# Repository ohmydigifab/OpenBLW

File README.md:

# OpenBLW
Open Biwa Lake Walker

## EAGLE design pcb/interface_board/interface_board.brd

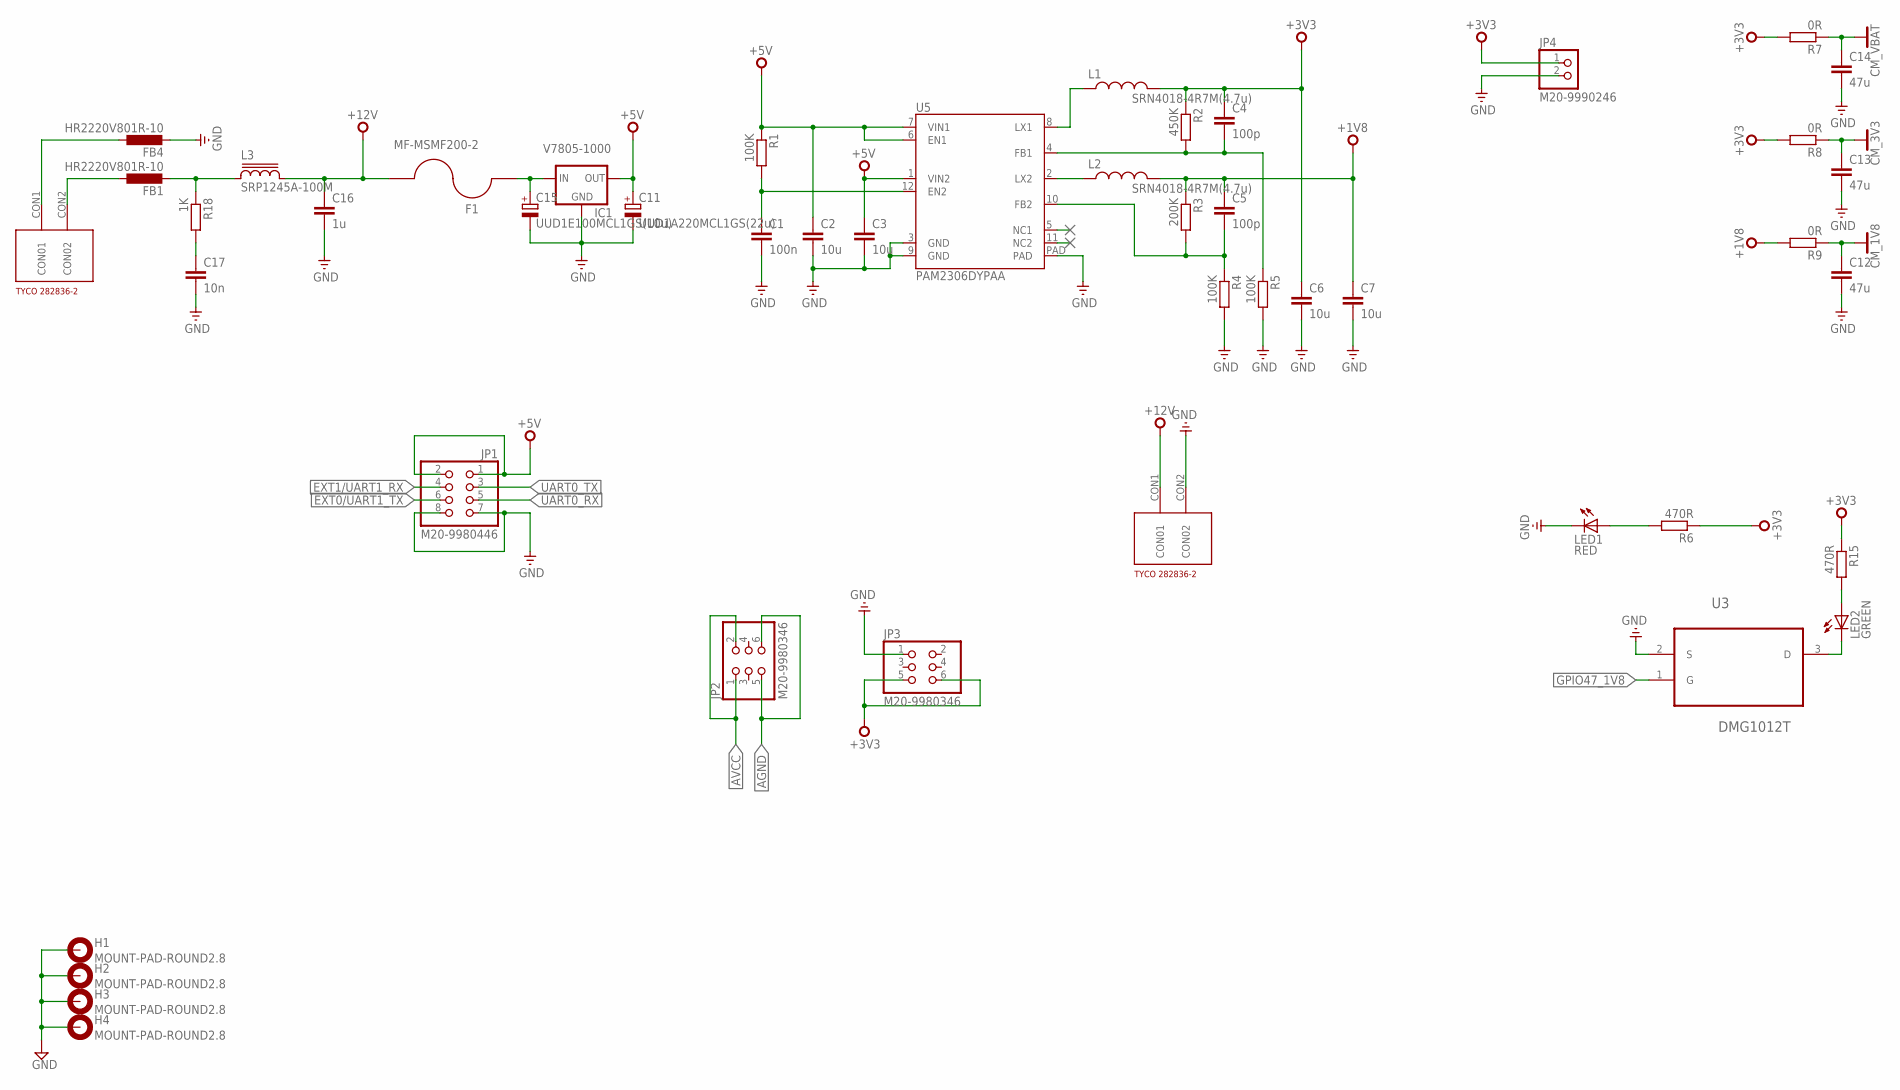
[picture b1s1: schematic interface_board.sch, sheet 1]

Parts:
C1: 100n; C0402
C2, C3, C6, C7: 10u; C0805
C4, C5: 100p; C0402
C11: UUD1A220MCL1GS(22u); 153CLV-0405
C12, C13, C14: 47u; C1206
C15: UUD1E100MCL1GS(10u); 153CLV-0405
C16: 1u; C0402
C17: 10n; C0402
F1: MF-MSMF200-2; 1812
FB1, FB4: HR2220V801R-10; L5650M
H1, H2, H3, H4: MOUNT-PAD-ROUND2.8; 2,8-PAD
IC1: V7805-1000; DIP_3PIN
JP1: M20-9980446; 2X04
JP2, JP3: M20-9980346; 2X03
JP4: M20-9990246; 1X02
L1, L2: SRN4018-4R7M(4.7u); BOURNS-SRN4018
L3: SRP1245A-100M; SRP1250A
LED1: RED; CHIP-LED0603
LED2: GREEN; CHIP-LED0603
R1, R4, R5: 100K; R0402
R2: 450K; R0402
R3: 200K; R0402
R6, R15: 470R; R0402
R7, R8, R9: 0R; R0805
R18: 1K; R0402
U3: DMG1012T; SOT523
U5: PAM2306DYPAA; WDFN3X3-12L
U$1: 282836-2
U$2: M20-9980346; 282836-2

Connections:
+1V8: C5.1, C7.1, L2.P$1 (1), R3.1, R9.2
+3V3: C4.1, C6.1, JP3.5, JP3.6, JP4.1, L1.P$1 (1), R2.1, R6.1, R7.2, R8.2, R15.1; also elsewhere on the board
+5V: C2.1, C3.1, C11.+, IC1.OUT, JP1.1, JP1.2, R1.1, U5.1 (VIN2), U5.6 (EN1), U5.7 (VIN1); also elsewhere on the board
+12V: C16.1, F1.1, L3.2, U$2.CON1 (CON01)
AGND: FB4.1, JP2.5, JP2.6, U$1.CON1 (CON01)
AVCC: FB1.1, JP2.1, JP2.2, U$1.CON2 (CON02)
CM_1V8: C12.1, R9.1; also elsewhere on the board
CM_3V3: C13.1, R8.1; also elsewhere on the board
CM_VBAT: C14.1, R7.1; also elsewhere on the board
EXT0/UART1_TX: JP1.6; also elsewhere on the board
EXT1/UART1_RX: JP1.4; also elsewhere on the board
GND: C1.2, C2.2, C3.2, C6.2, C7.2, C11.-, C12.2, C13.2, C14.2, C15.-, C16.2, C17.2, FB4.2, H1.B2,8, H2.B2,8, H3.B2,8, H4.B2,8, IC1.GND, JP1.7, JP1.8, JP3.1, JP4.2, LED1.C, R4.2, R5.2, U3.2 (S), U5.3 (GND), U5.9 (GND), U5.PAD, U$2.CON2 (CON02); also elsewhere on the board
GPIO47_1V8: U3.1 (G); also elsewhere on the board
unnamed: C1.1, R1.2, U5.12 (EN2)
unnamed: L1.P$2 (2), U5.8 (LX1)
unnamed: FB1.2, L3.1, R18.1
unnamed: L2.P$2 (2), U5.2 (LX2)
unnamed: C4.2, R2.2, R5.1, U5.4 (FB1)
unnamed: LED1.A, R6.2
unnamed: C5.2, R3.2, R4.1, U5.10 (FB2)
unnamed: LED2.A, R15.2
unnamed: LED2.C, U3.3 (D)
unnamed: C17.1, R18.2
unnamed: C15.+, F1.2, IC1.IN
UART0_RX: JP1.5; also elsewhere on the board
UART0_TX: JP1.3; also elsewhere on the board

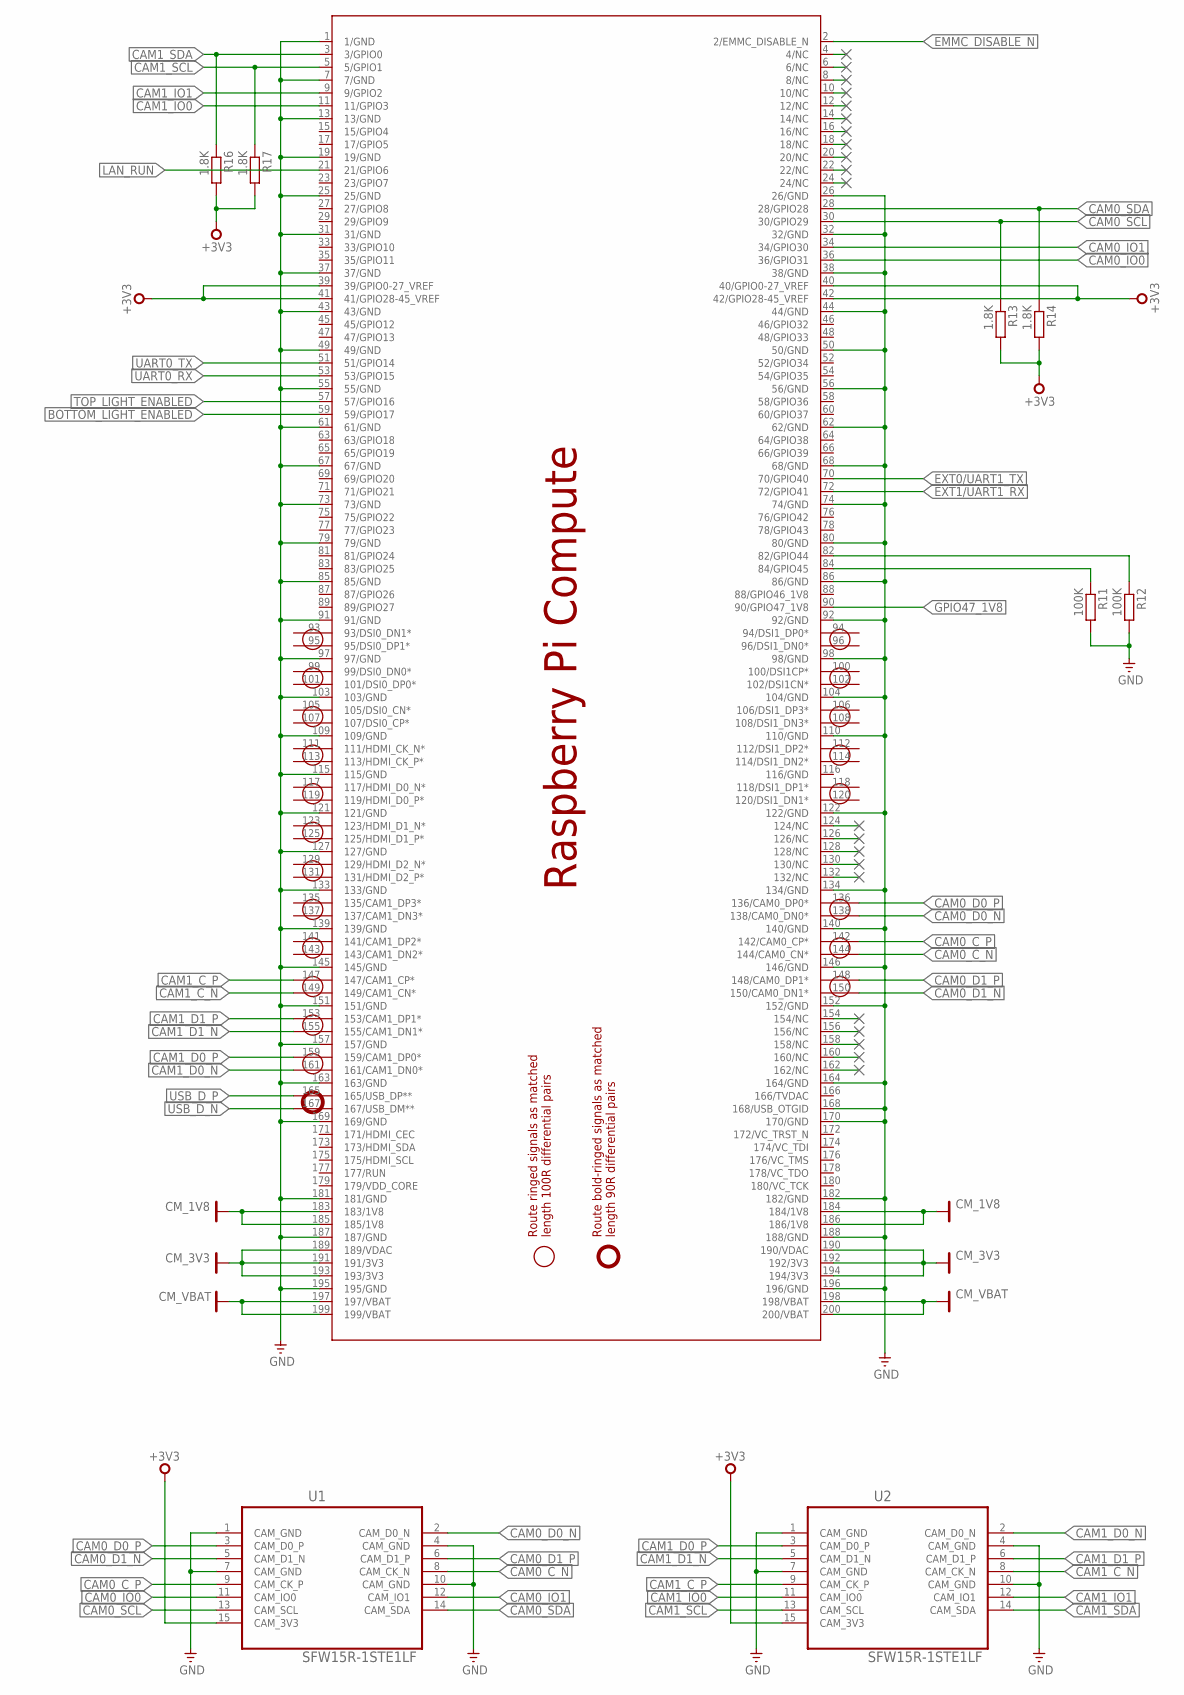
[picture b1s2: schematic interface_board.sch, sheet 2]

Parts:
PCB1: 1473005-4; RPI_COMPUTE
R11, R12: 100K; R0402
R13, R14, R16, R17: 1.8K; R0402
U1, U2: SFW15R-1STE1LF; RPI_CAMERA

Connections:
+3V3: PCB1.39 (39/GPIO0-27_VREF), PCB1.40 (40/GPIO0-27_VREF), PCB1.41 (41/GPIO28-45_VREF), PCB1.42 (42/GPIO28-45_VREF), R13.2, R14.2, R16.2, R17.2, U1.15 (CAM_3V3), U2.15 (CAM_3V3); also elsewhere on the board
BOTTOM_LIGHT_ENABLED: PCB1.59 (59/GPIO17)
CAM0_C_N: PCB1.144 (144/CAM0_CN*), U1.8 (CAM_CK_N)
CAM0_C_P: PCB1.142 (142/CAM0_CP*), U1.9 (CAM_CK_P)
CAM0_D0_N: PCB1.138 (138/CAM0_DN0*), U1.2 (CAM_D0_N)
CAM0_D0_P: PCB1.136 (136/CAM0_DP0*), U1.3 (CAM_D0_P)
CAM0_D1_N: PCB1.150 (150/CAM0_DN1*), U1.5 (CAM_D1_N)
CAM0_D1_P: PCB1.148 (148/CAM0_DP1*), U1.6 (CAM_D1_P)
CAM0_IO0: PCB1.36 (36/GPIO31), U1.11 (CAM_IO0)
CAM0_IO1: PCB1.34 (34/GPIO30), U1.12 (CAM_IO1)
CAM0_SCL: PCB1.30 (30/GPIO29), R13.1, U1.13 (CAM_SCL)
CAM0_SDA: PCB1.28 (28/GPIO28), R14.1, U1.14 (CAM_SDA)
CAM1_C_N: PCB1.149 (149/CAM1_CN*), U2.8 (CAM_CK_N)
CAM1_C_P: PCB1.147 (147/CAM1_CP*), U2.9 (CAM_CK_P)
CAM1_D0_N: PCB1.161 (161/CAM1_DN0*), U2.2 (CAM_D0_N)
CAM1_D0_P: PCB1.159 (159/CAM1_DP0*), U2.3 (CAM_D0_P)
CAM1_D1_N: PCB1.155 (155/CAM1_DN1*), U2.5 (CAM_D1_N)
CAM1_D1_P: PCB1.153 (153/CAM1_DP1*), U2.6 (CAM_D1_P)
CAM1_IO0: PCB1.11 (11/GPIO3), U2.11 (CAM_IO0)
CAM1_IO1: PCB1.9 (9/GPIO2), U2.12 (CAM_IO1)
CAM1_SCL: PCB1.5 (5/GPIO1), R17.1, U2.13 (CAM_SCL)
CAM1_SDA: PCB1.3 (3/GPIO0), R16.1, U2.14 (CAM_SDA)
CM_1V8: PCB1.183 (183/1V8), PCB1.184 (184/1V8), PCB1.185 (185/1V8), PCB1.186 (186/1V8); also elsewhere on the board
CM_3V3: PCB1.189 (189/VDAC), PCB1.190 (190/VDAC), PCB1.191 (191/3V3), PCB1.192 (192/3V3), PCB1.193 (193/3V3), PCB1.194 (194/3V3); also elsewhere on the board
CM_VBAT: PCB1.197 (197/VBAT), PCB1.198 (198/VBAT), PCB1.199 (199/VBAT), PCB1.200 (200/VBAT); also elsewhere on the board
EMMC_DISABLE_N: PCB1.2 (2/EMMC_DISABLE_N)
EXT0/UART1_TX: PCB1.70 (70/GPIO40); also elsewhere on the board
EXT1/UART1_RX: PCB1.72 (72/GPIO41); also elsewhere on the board
GND: PCB1.1 (1/GND), PCB1.7 (7/GND), PCB1.13 (13/GND), PCB1.19 (19/GND), PCB1.25 (25/GND), PCB1.26 (26/GND), PCB1.31 (31/GND), PCB1.32 (32/GND), PCB1.37 (37/GND), PCB1.38 (38/GND), PCB1.43 (43/GND), PCB1.44 (44/GND), PCB1.49 (49/GND), PCB1.50 (50/GND), PCB1.55 (55/GND), PCB1.56 (56/GND), PCB1.61 (61/GND), PCB1.62 (62/GND), PCB1.67 (67/GND), PCB1.68 (68/GND), PCB1.73 (73/GND), PCB1.74 (74/GND), PCB1.79 (79/GND), PCB1.80 (80/GND), PCB1.85 (85/GND), PCB1.86 (86/GND), PCB1.91 (91/GND), PCB1.92 (92/GND), PCB1.97 (97/GND), PCB1.98 (98/GND), PCB1.103 (103/GND), PCB1.104 (104/GND), PCB1.109 (109/GND), PCB1.110 (110/GND), PCB1.115 (115/GND), PCB1.121 (121/GND), PCB1.122 (122/GND), PCB1.127 (127/GND), PCB1.133 (133/GND), PCB1.134 (134/GND), PCB1.139 (139/GND), PCB1.140 (140/GND), PCB1.145 (145/GND), PCB1.146 (146/GND), PCB1.151 (151/GND), PCB1.152 (152/GND), PCB1.157 (157/GND), PCB1.163 (163/GND), PCB1.164 (164/GND), PCB1.168 (168/USB_OTGID), PCB1.169 (169/GND), PCB1.170 (170/GND), PCB1.181 (181/GND), PCB1.182 (182/GND), PCB1.187 (187/GND), PCB1.188 (188/GND), PCB1.195 (195/GND), PCB1.196 (196/GND), R11.2, R12.2, U1.1 (CAM_GND), U1.4 (CAM_GND), U1.7 (CAM_GND), U1.10 (CAM_GND), U2.1 (CAM_GND), U2.4 (CAM_GND), U2.7 (CAM_GND), U2.10 (CAM_GND); also elsewhere on the board
GPIO47_1V8: PCB1.90 (90/GPIO47_1V8); also elsewhere on the board
LAN_RUN: PCB1.21 (21/GPIO6); also elsewhere on the board
unnamed: PCB1.82 (82/GPIO44), R12.1
unnamed: PCB1.84 (84/GPIO45), R11.1
TOP_LIGHT_ENABLED: PCB1.57 (57/GPIO16)
UART0_RX: PCB1.53 (53/GPIO15); also elsewhere on the board
UART0_TX: PCB1.51 (51/GPIO14); also elsewhere on the board
USB_D_N: PCB1.167 (167/USB_DM**); also elsewhere on the board
USB_D_P: PCB1.165 (165/USB_DP**); also elsewhere on the board

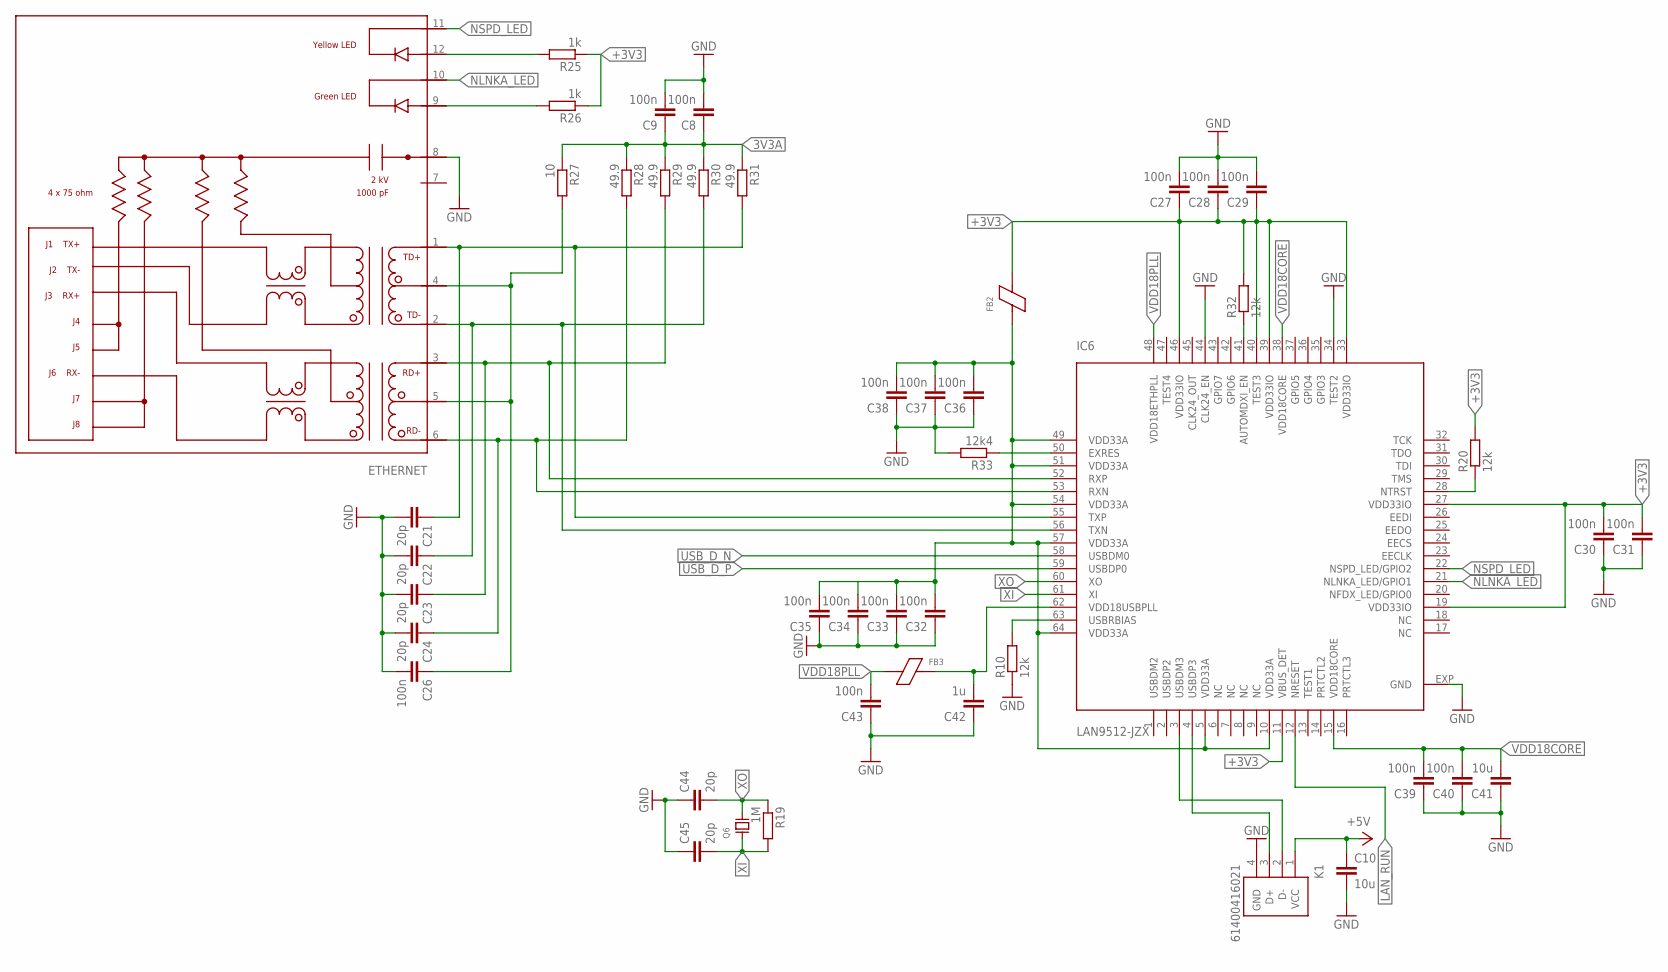
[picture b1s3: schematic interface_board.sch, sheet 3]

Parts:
C8, C9, C26, C27, C28, C29, C30, C31, C32, C33, C34, C35, C36, C37, C38, C39, C40, C43: 100n; C0603
C10, C41: 10u; C0805
C21, C22, C23, C24, C44, C45: 20p; C0603
C42: 1u; C0805
ETHERNET: HR911105A; RJ45
FB2, FB3: 742792022; C0805
IC6: LAN9512-JZX; QFN64-9X9
K1: 61400416021
Q6: CTS_32X25_SMD; CTS_32X25
R10, R20, R32: 12k; R0603
R19: 1M; R0603
R25, R26: 1k; R0603
R27: 10; R0603
R28, R29, R30, R31: 49.9; R0603
R33: 12k4; R0603

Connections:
3V3A: C8.1, C9.1, R27.1, R28.1, R29.1, R30.1, R31.1
3V3A1: C32.2, C33.2, C34.2, C35.2, C36.2, C37.2, C38.2, FB2.1, IC6.5 (VDD33A), IC6.10 (VDD33A), IC6.49 (VDD33A), IC6.51 (VDD33A), IC6.54 (VDD33A), IC6.57 (VDD33A), IC6.64 (VDD33A)
+3V3: C27.1, C28.1, C29.1, C30.2, C31.2, FB2.2, IC6.11 (VBUS_DET), IC6.19 (VDD33IO), IC6.27 (VDD33IO), IC6.33 (VDD33IO), IC6.39 (VDD33IO), IC6.40 (TEST3), IC6.46 (VDD33IO), R20.2, R25.1, R26.1, R32.2; also elsewhere on the board
+5V: C10.1, K1.1 (VCC); also elsewhere on the board
GND: C8.2, C9.2, C10.2, C21.2, C22.2, C23.2, C24.2, C26.2, C27.2, C28.2, C29.2, C30.1, C31.1, C32.1, C33.1, C34.1, C35.1, C36.1, C37.1, C38.1, C39.1, C40.1, C41.1, C42.1, C43.1, C44.1, C45.1, ETHERNET.8, IC6.34 (TEST2), IC6.44 (CLK24_EN), IC6.EXP (GND), K1.4 (GND), R10.1, R33.2; also elsewhere on the board
LAN_RUN: IC6.12 (NRESET); also elsewhere on the board
unnamed: ETHERNET.12, R25.2
unnamed: ETHERNET.9, R26.2
unnamed: C26.1, ETHERNET.4, ETHERNET.5, R27.2
unnamed: IC6.63 (USBRBIAS), R10.2
unnamed: C42.2, FB3.2, IC6.62 (VDD18USBPLL)
unnamed: IC6.41 (AUTOMDXI_EN), R32.1
unnamed: IC6.50 (EXRES), R33.1
unnamed: IC6.28 (NTRST), R20.1
NLNKA_LED: ETHERNET.10, IC6.21 (NLNKA_LED/GPIO1)
NSPD_LED: ETHERNET.11, IC6.22 (NSPD_LED/GPIO2)
RX_N: C24.1, ETHERNET.6, IC6.53 (RXN), R28.2
RX_P: C23.1, ETHERNET.3, IC6.52 (RXP), R29.2
TX_N: C22.1, ETHERNET.2, IC6.56 (TXN), R30.2
TX_P: C21.1, ETHERNET.1, IC6.55 (TXP), R31.2
USBD3_N: IC6.3 (USBDM3), K1.2 (D-)
USBD3_P: IC6.4 (USBDP3), K1.3 (D+)
USB_D_N: IC6.58 (USBDM0); also elsewhere on the board
USB_D_P: IC6.59 (USBDP0); also elsewhere on the board
VDD18CORE: C39.2, C40.2, C41.2, IC6.15 (VDD18CORE), IC6.38 (VDD18CORE)
VDD18PLL: C43.2, FB3.1, IC6.48 (VDD18ETHPLL)
XI: C45.2, IC6.61 (XI), Q6.1 (X1), R19.2
XO: C44.2, IC6.60 (XO), Q6.3 (X2), R19.1

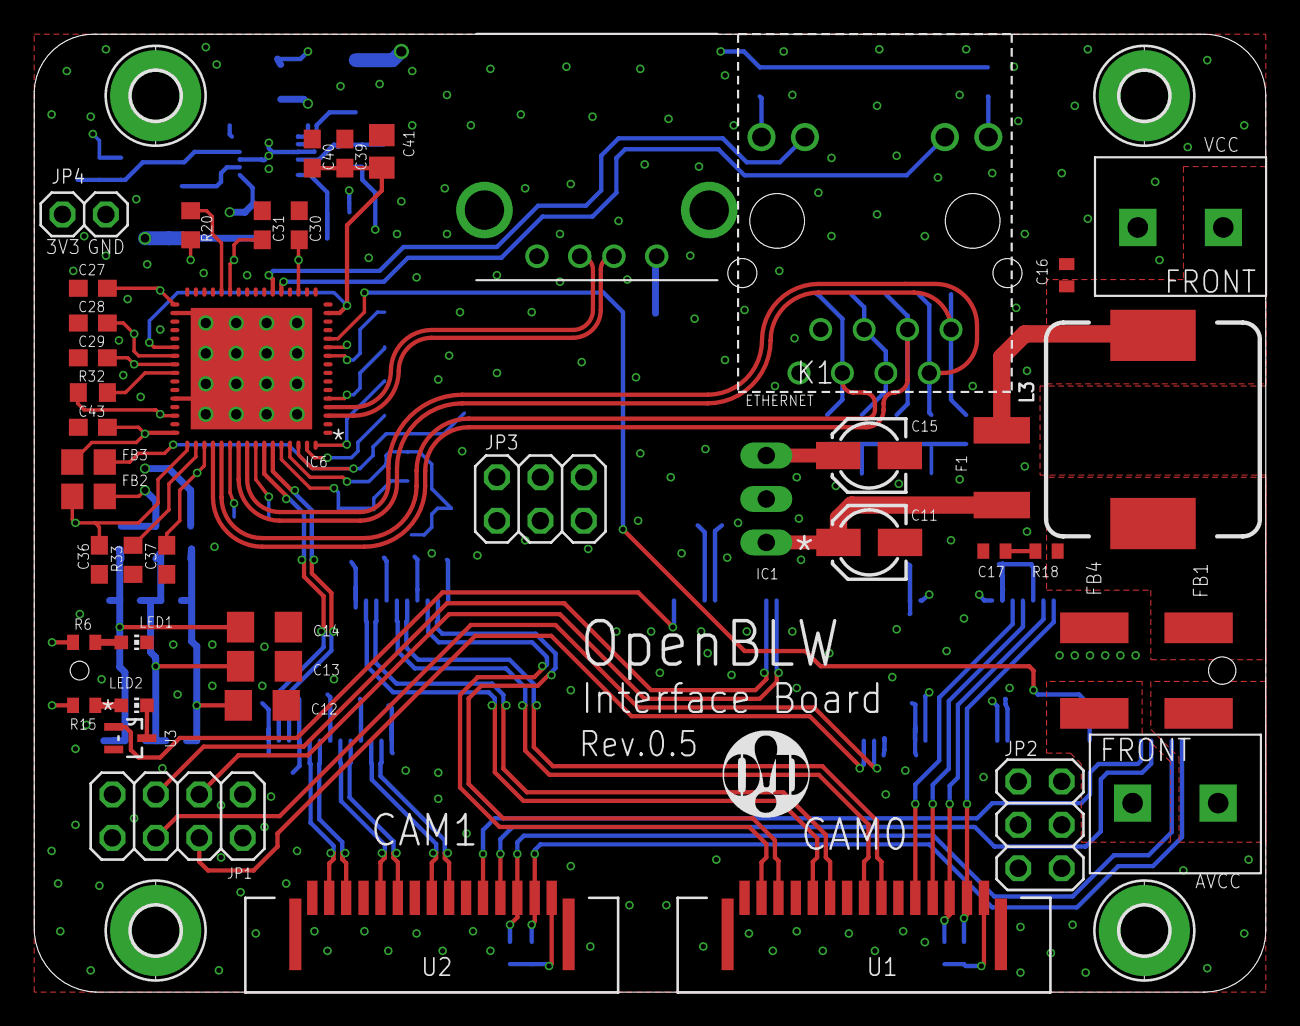
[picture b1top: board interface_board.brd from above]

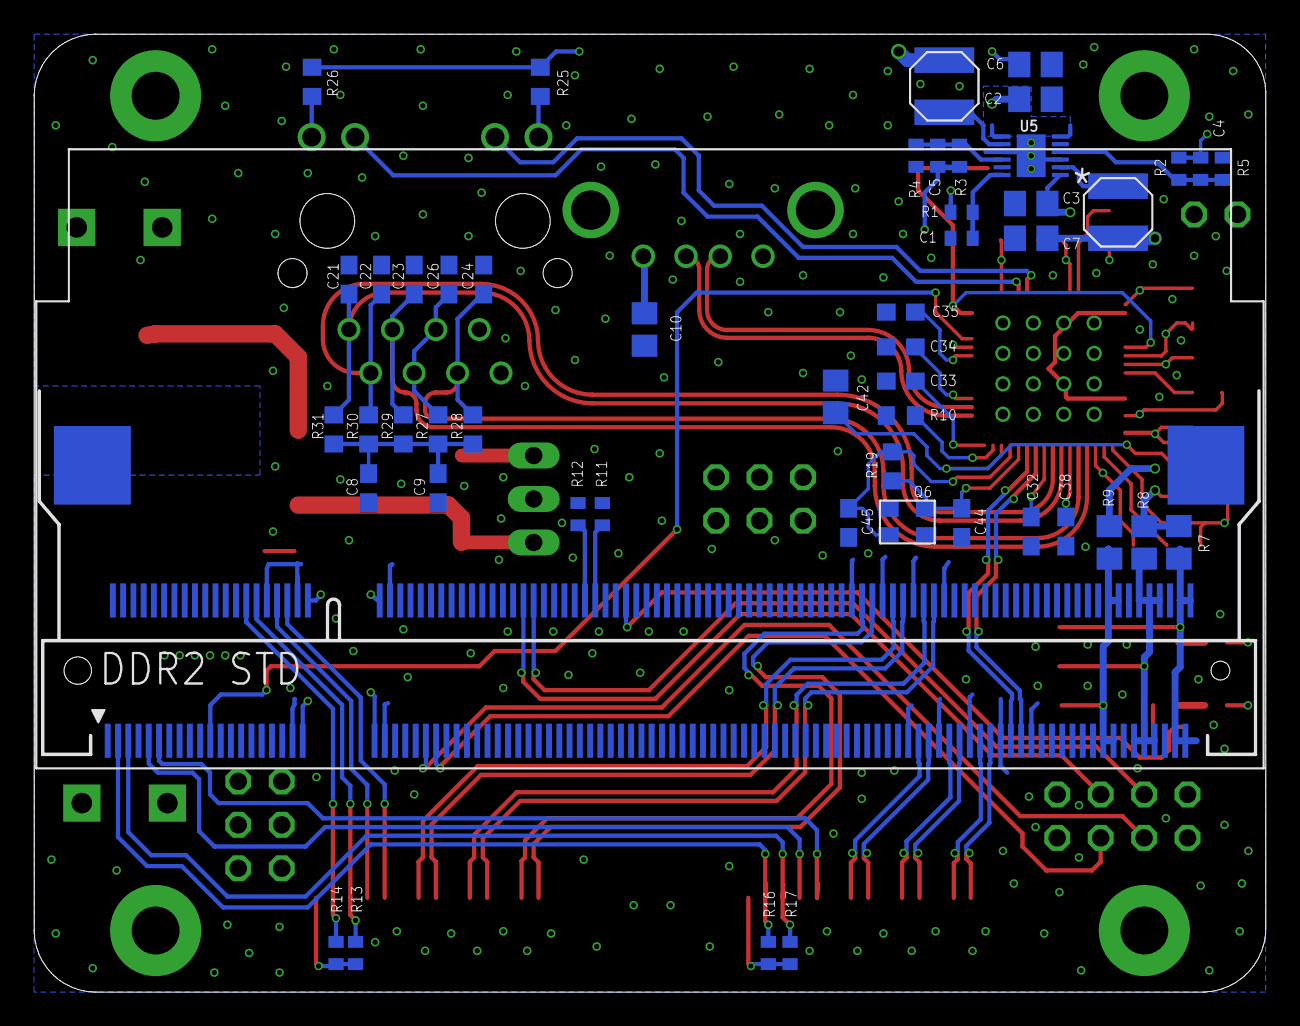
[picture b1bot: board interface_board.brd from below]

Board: 4 copper layers, 72.0 x 56.0 mm, 102 parts (51 on the bottom side), 73 nets.

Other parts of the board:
LOGO1: OHMYDIGIFAB_LOGO
U$3: TENDA_P200

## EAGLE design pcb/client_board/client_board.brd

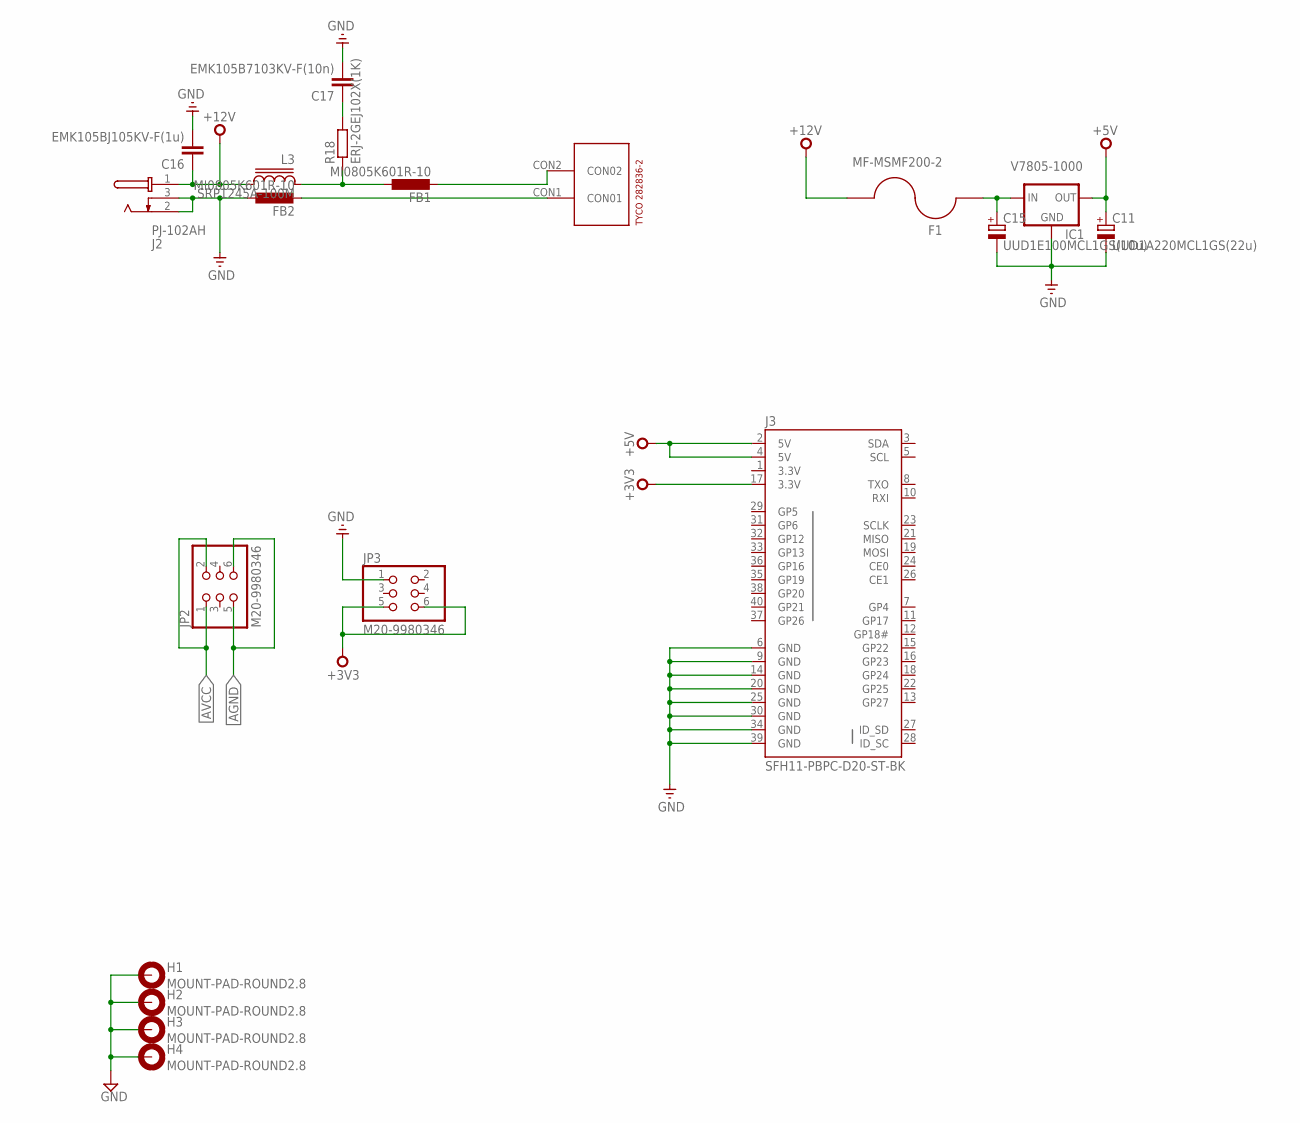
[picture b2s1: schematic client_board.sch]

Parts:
C11: UUD1A220MCL1GS(22u); 153CLV-0405
C15: UUD1E100MCL1GS(10u); 153CLV-0405
C16: EMK105BJ105KV-F(1u); C0402
C17: EMK105B7103KV-F(10n); C0402
F1: MF-MSMF200-2; 1812
FB1, FB2: MI0805K601R-10; L5650M
H1, H2, H3, H4: MOUNT-PAD-ROUND2.8; 2,8-PAD
IC1: V7805-1000; DIP_3PIN
J2: PJ-102AH; PJ-102XH
J3: SFH11-PBPC-D20-ST-BK; 2X20-SHROUDED
JP2, JP3: M20-9980346; 2X03
L3: SRP1245A-100M; SRP1250A
R18: ERJ-2GEJ102X(1K); R0402
U$1: 282836-2

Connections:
3.3V: J3.1 (3.3V)
+3V3: J3.17 (3.3V), JP3.5, JP3.6
+5V: C11.+, IC1.OUT, J3.2 (5V), J3.4 (5V)
+12V: C16.1, F1.1, J2.1 (T), L3.2
AGND: FB2.2, JP2.5, JP2.6, U$1.CON1 (CON01)
AVCC: FB1.2, JP2.1, JP2.2, U$1.CON2 (CON02)
GND: C11.-, C15.-, C16.2, C17.2, FB2.1, H1.B2,8, H2.B2,8, H3.B2,8, H4.B2,8, IC1.GND, J2.2 (S), J2.3 (SS), J3.6 (GND), J3.9 (GND), J3.14 (GND), J3.20 (GND), J3.25 (GND), J3.30 (GND), J3.34 (GND), J3.39 (GND), JP3.1
unnamed: C15.+, F1.2, IC1.IN
unnamed: FB1.1, L3.1, R18.1
unnamed: C17.1, R18.2

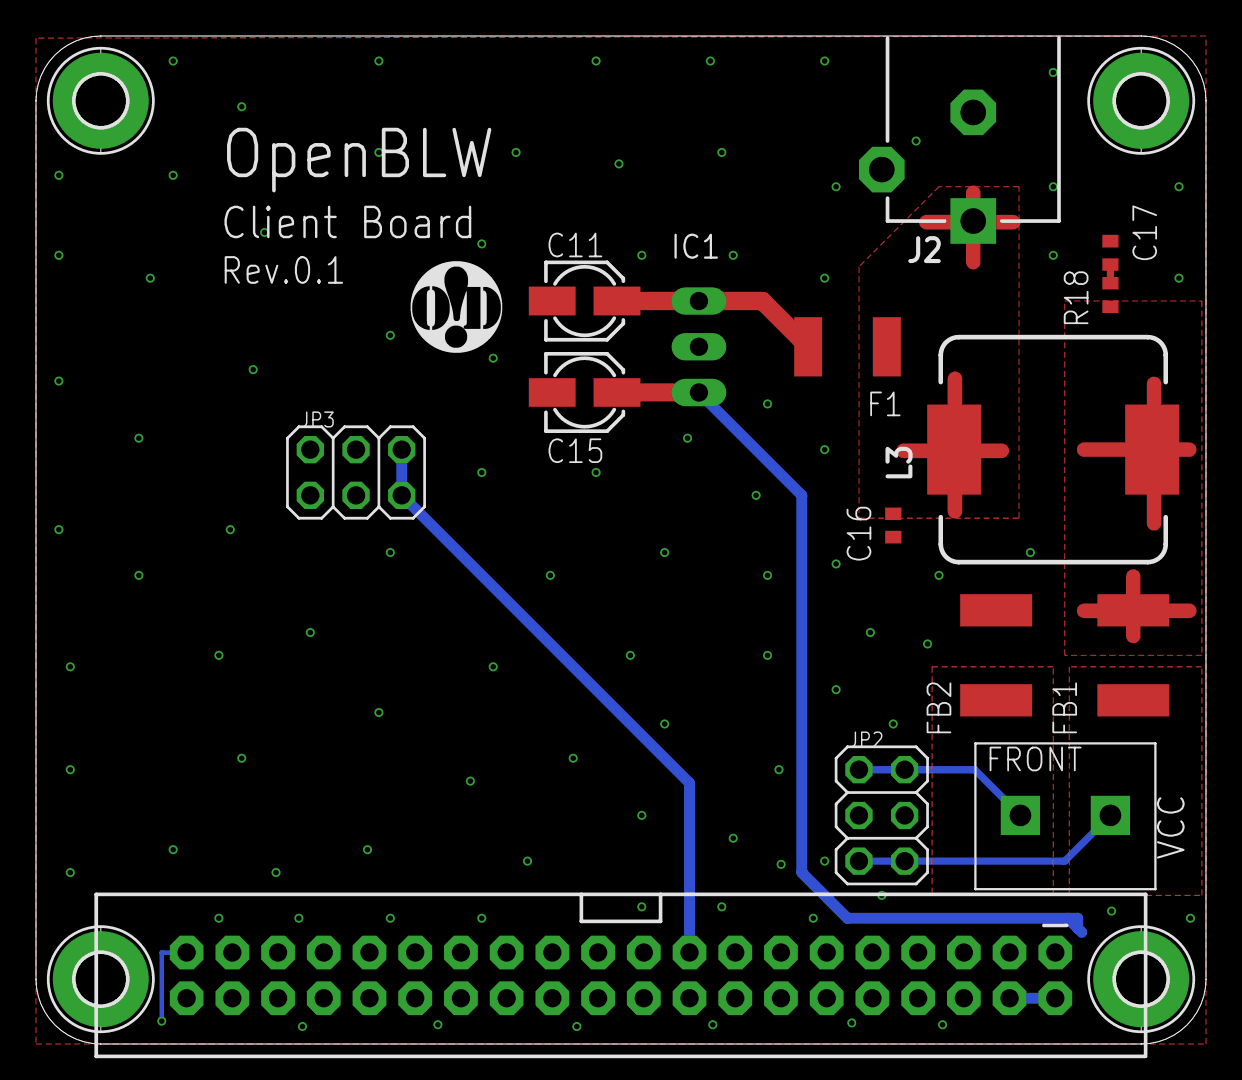
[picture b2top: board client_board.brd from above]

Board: 4 copper layers, 65.0 x 56.0 mm, 21 parts (0 on the bottom side), 9 nets.

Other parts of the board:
LOGO1: OHMYDIGIFAB_LOGO
U$2: TENDA_P200

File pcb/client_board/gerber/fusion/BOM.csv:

Part/Designator,Manufacture Part Number/Seeed SKU,QuantityC17,EMK105B7103KV-F,1C15,UUD1E100MCL1GS,1R18,ERJ-2GEJ102X,1C16,EMK105BJ105KV-F,1C11,UUD1A220MCL1GS,1U$1,282836-2,1F1,MF-MSMF200-2,1"FB1, FB2",HR2220V801R-10,2J2,PJ-102AH,1J3,SFH11-PBPC-D20-ST-BK,1L3,SRP1245A-100M,1"JP2, JP3",M20-9980346,2IC1,V7805-1000,1

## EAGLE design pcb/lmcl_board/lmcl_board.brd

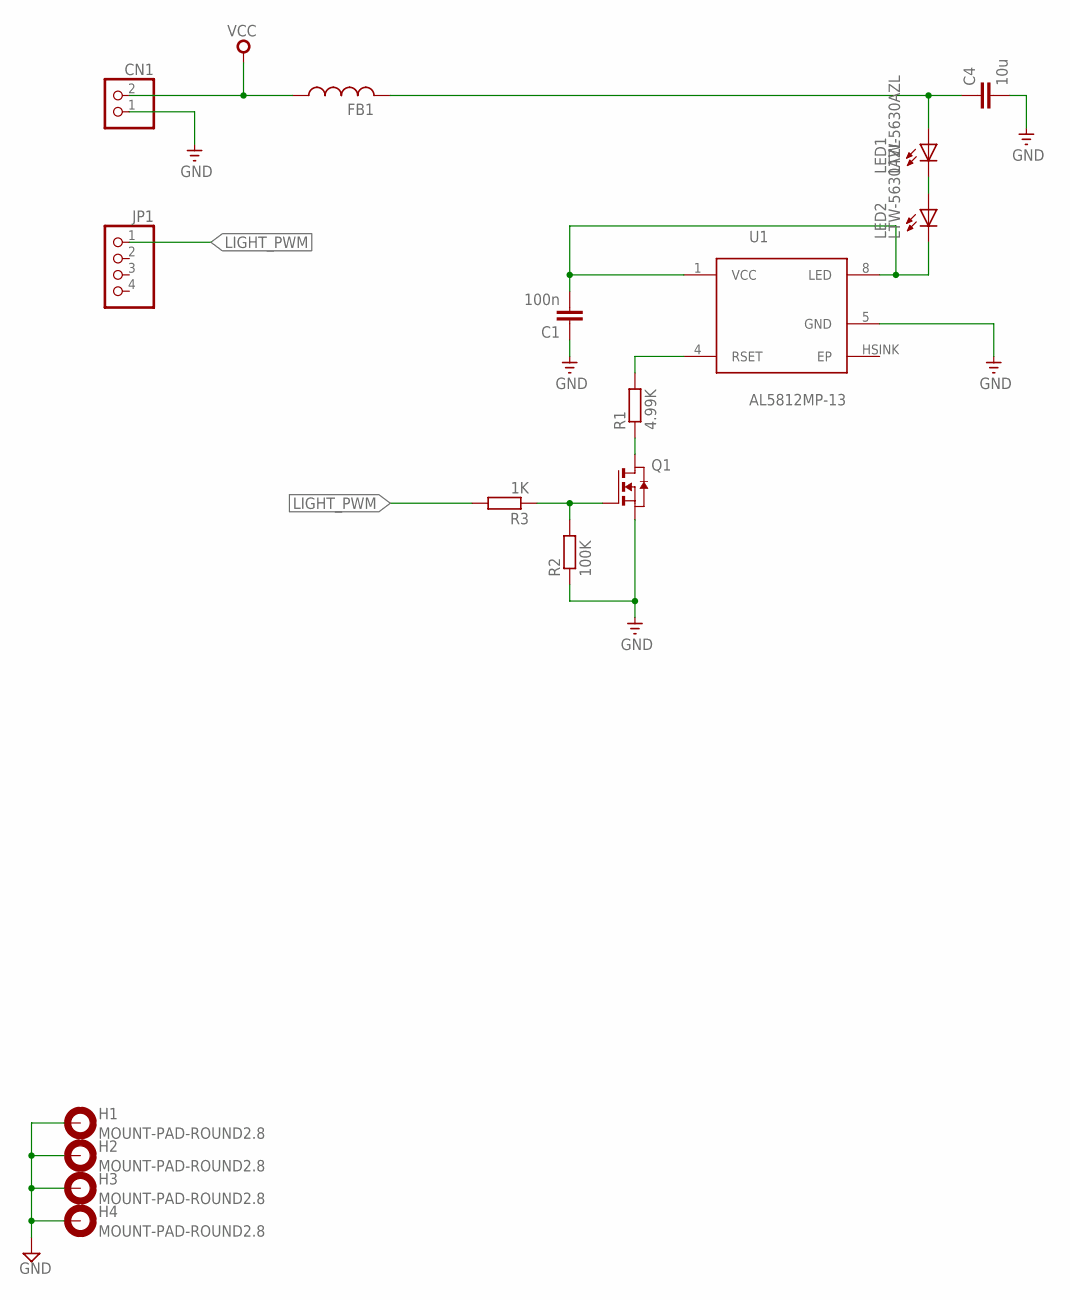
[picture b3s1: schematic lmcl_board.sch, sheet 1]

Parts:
C1: 100n; C0402
C4: 10u; C0402
CN1: JST_2PIN-THM; JST-PH-2-THM
FB1: FERRITESIZE_0805; R0805
H1, H2, H3, H4: MOUNT-PAD-ROUND2.8; 2,8-PAD
JP1: PINHD-1X4; 1X04
LED1, LED2: LTW-5630AZL; LITEON-5630
Q1: NMOS-FETSOT23; SOT23
R1: 4.99K; R0402
R2: 100K; R0402
R3: 1K; R0402
U1: AL5812MP-13; MSOP-8EP

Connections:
GND: C1.1, C4.2, CN1.1 (2), H1.B2,8, H2.B2,8, H3.B2,8, H4.B2,8, Q1.2 (S), R2.1, U1.5 (GND); also elsewhere on the board
LIGHT_PWM: JP1.1, R3.2
unnamed: LED1.C1 (C), LED1.C2 (C), LED2.A1 (A), LED2.A2 (A), LED2.A3 (A)
unnamed: C1.2, LED2.C1 (C), LED2.C2 (C), U1.1 (VCC), U1.8 (LED)
unnamed: C4.1, FB1.2, LED1.A1 (A), LED1.A2 (A), LED1.A3 (A)
unnamed: R1.2, U1.4 (RSET)
unnamed: Q1.3 (D), R1.1
unnamed: Q1.1 (G), R2.2, R3.1
VCC: CN1.2 (1), FB1.1; also elsewhere on the board

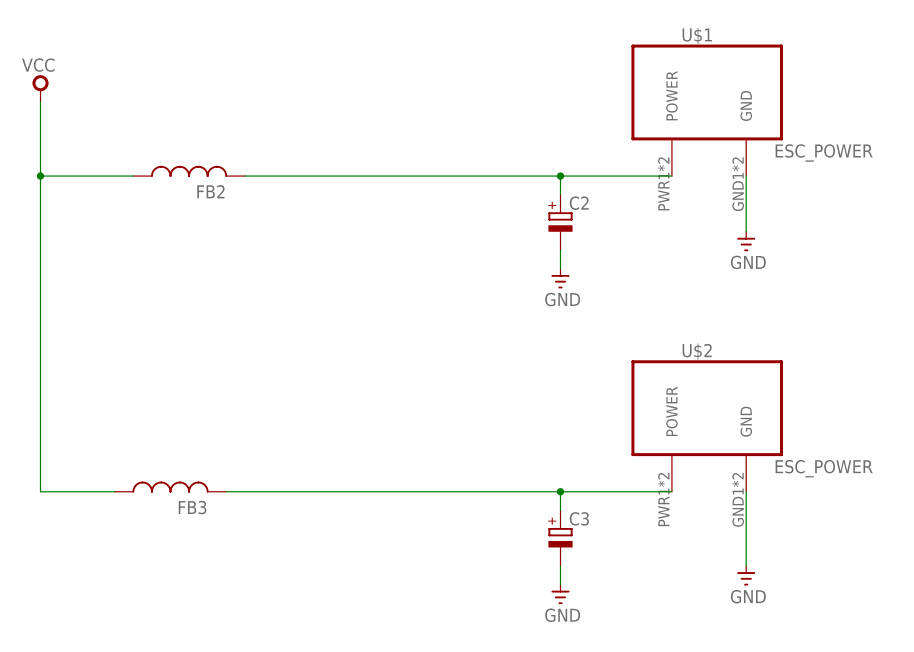
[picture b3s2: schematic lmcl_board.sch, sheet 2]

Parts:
C2, C3: CPOL-EU153CLV-0810; 153CLV-0810
FB2, FB3: FERRITESIZE_0805; R0805
U$1, U$2: ESC_POWER

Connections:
GND: C2.-, C3.-, U$1.GND1 (GND), U$1.GND2 (GND), U$2.GND1 (GND), U$2.GND2 (GND); also elsewhere on the board
unnamed: C3.+, FB3.2, U$2.PWR1 (POWER), U$2.PWR2 (POWER)
unnamed: C2.+, FB2.2, U$1.PWR1 (POWER), U$1.PWR2 (POWER)
VCC: FB2.1, FB3.1; also elsewhere on the board

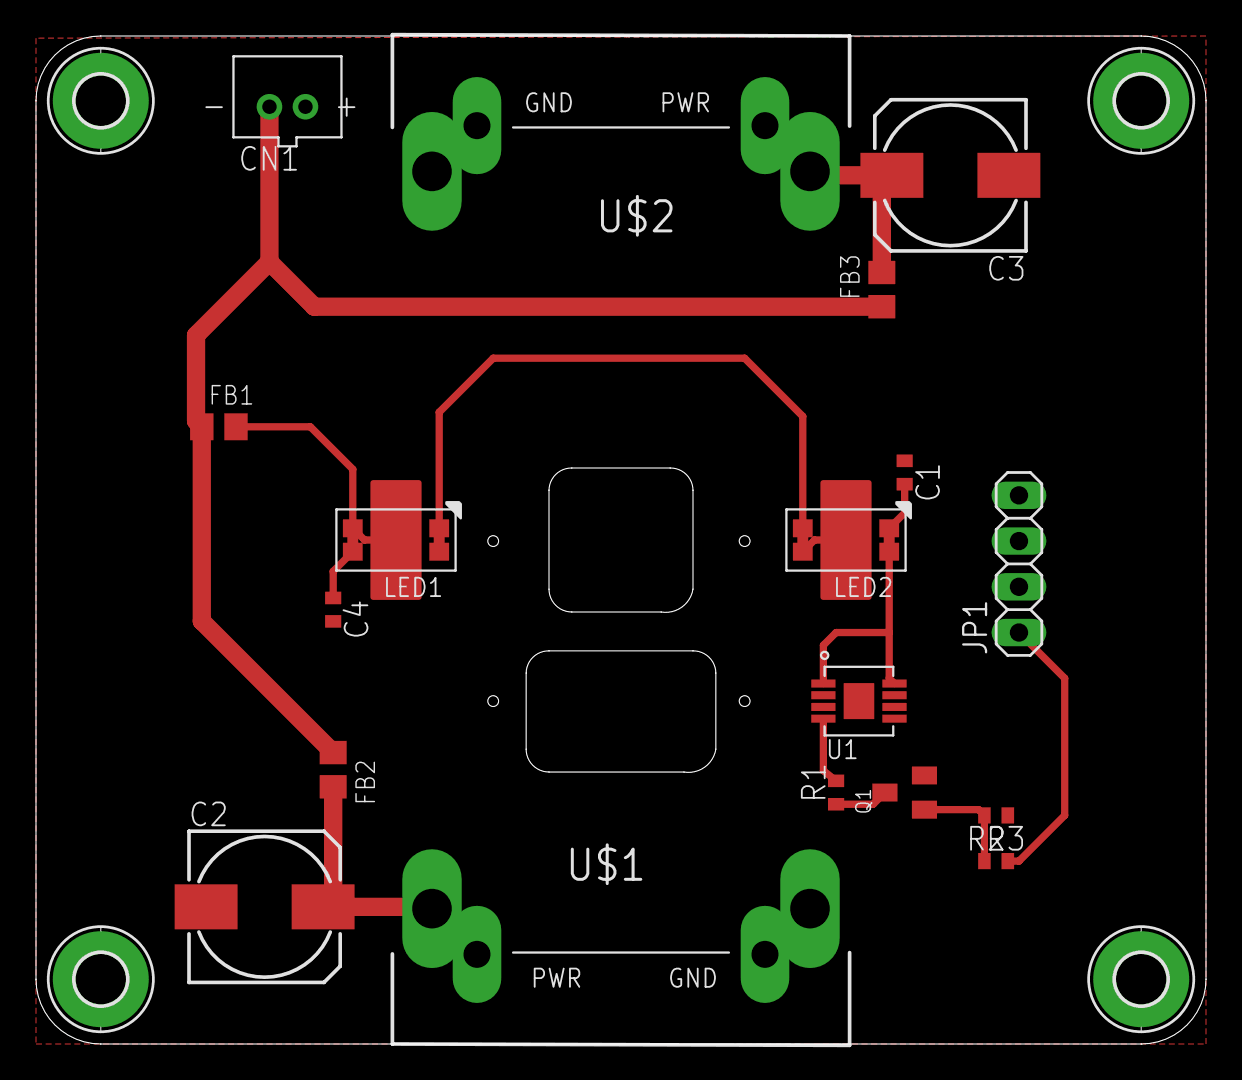
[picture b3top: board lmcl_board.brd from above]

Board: 4 copper layers, 65.0 x 56.0 mm, 22 parts (0 on the bottom side), 11 nets.

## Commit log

2015-08-06 init
2015-08-06 image
2015-08-06 ignore
2015-08-07 prop
2015-08-08 bot_nut_spacer
2015-08-08 improved arm
2015-08-08 update image
2015-08-09 prop_shroud
2015-08-20 bugfix
2015-08-20 v0.1
2015-08-20 v0.1.1
2015-08-20 resolution tuning
2015-08-20 v0.2a
2015-08-20 replace image
2015-08-21 round corner
2015-08-22 number of bolt has been changed
2015-08-22 tuning dxf file
2015-08-24 shorten prop_shroud
2015-08-27 tiny modification
2015-08-31 compatibility of 150mm and 100mm
2015-09-08 raspi A+ version
2015-09-24 Raspi A+ prototype
2015-09-24 parametalize PROP_SHROUD_DIA
2015-09-26 baseplate improved num of prop blades got 6
2015-10-05 use minkowski
2015-10-09 camera holder
2015-10-09 prop.stl
2015-10-09 design change of upper arm
2015-10-09 image & parametric
2015-12-03 server
2015-12-05 openpilot
2015-12-05 bufix
2015-12-05 add openpilot_definitions
2015-12-14 test
2015-12-14 arm_test
2015-12-15 split array
2015-12-15 revert
2015-12-16 meta test
2015-12-16 meta
2015-12-16 refactoring
2015-12-17 connect
2015-12-17 bugifx
2015-12-17 op.init
2015-12-19 setControlValue
2015-12-20 actuator
2015-12-21 level
2015-12-21 bias off
2015-12-21 console
2016-01-04 proxy
2016-01-15 small modifications
2016-01-15 doble side
2016-01-15 symmetric
2016-01-15 yaw lock
2016-01-15 performance tuning
2016-01-15 up side down
2016-01-24 eagle cad files
2016-01-24 reference
2016-01-25 add dc-dc
2016-01-30 porovisional wiring
2016-02-01 rev0.1
2016-02-02 before export gerber
2016-02-02 before order 0
2016-02-03 0.5mm clearance
2016-02-03 order
2016-02-05 lmcl_board
2016-02-08 fusion
2016-02-08 outline
2016-02-08 partslist
2016-02-09 rename
2016-02-12 client board
2016-02-13 rj45
2016-02-13 tune
2016-02-13 tochu
2016-02-16 before order pcbs
2016-02-16 parts miss
2016-02-17 ordered
2016-03-08 modification of package.json
2016-03-16 jpeg
2016-03-17 uv4l
2016-03-17 debug
2016-03-18 vrcam
2016-03-18 toEquirectangular
2016-03-18 performance
2016-03-30 setRotation, piblaster
2016-03-31 capture
2016-03-31 interface_board
2016-03-31 vr.mp4
2016-03-31 recording
2016-03-31 filename
2016-04-01 stoprecord
2016-04-06 cam separate
2016-04-07 swap cam
2016-04-07 wait cam startup
2016-04-07 cam tune
2016-04-07 1 min movie
2016-04-07 del h264
2016-04-25 extlens_holder

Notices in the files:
parts and their libraries:
SparkFun-Boards: Licensing: Creative Commons ShareAlike 4.0 International - https://creativecommons.org/licenses/by-sa/4.0
con-dc-power: Copyright (C) 2015, Bob Starr
dports: Copyright (C) 2008, Bob Starr
supply0: Copyright (C) 2007, Bob Starr
